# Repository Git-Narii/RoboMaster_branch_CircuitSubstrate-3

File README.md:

24Vの電源及びCAN通信の信号線を分岐させる基板

3つまでのロボマスモータに対応

裏側のみの使用

4ピンの5Vはエナメル線などで追加接続が必要

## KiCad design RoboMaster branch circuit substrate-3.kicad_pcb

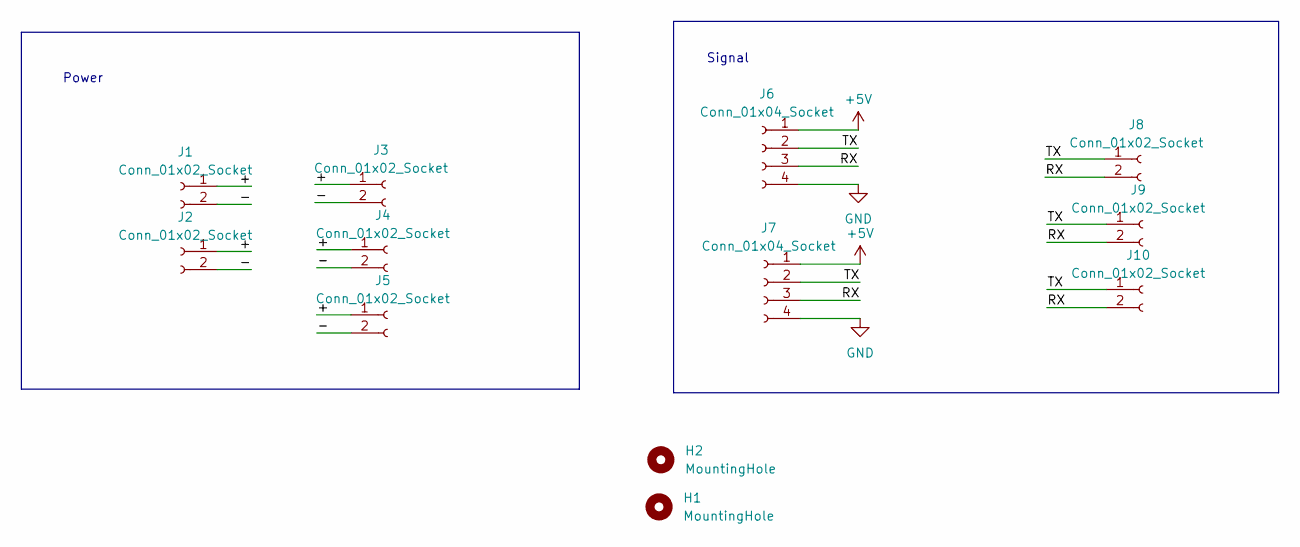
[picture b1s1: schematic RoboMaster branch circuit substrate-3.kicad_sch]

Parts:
H1, H2: MountingHole; MountingHole_3.2mm_M3
J1: Conn_01x02_Socket; AMASS_XT60PW-F_1x02_P7.20mm_Horizontal
J2: Conn_01x02_Socket; AMASS_XT60PW-M_1x02_P7.20mm_Horizontal
J3, J4, J5: Conn_01x02_Socket; AMASS_XT30U-F_1x02_P5.0mm_Vertical
J6, J7: Conn_01x04_Socket; JST_XA_S04B-XASK-1_1x04_P2.50mm_Horizontal
J8, J9, J10: Conn_01x02_Socket; JST_XA_B02B-XASK-1_1x02_P2.50mm_Vertical

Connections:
+5V: J6.1, J7.1
/+: J1.1, J2.1, J3.1, J4.1, J5.1
/-: J1.2, J2.2, J3.2, J4.2, J5.2
/RX: J6.3, J7.3, J8.2, J9.2, J10.2
/TX: J6.2, J7.2, J8.1, J9.1, J10.1
GND: J6.4, J7.4

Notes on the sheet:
Power
Signal

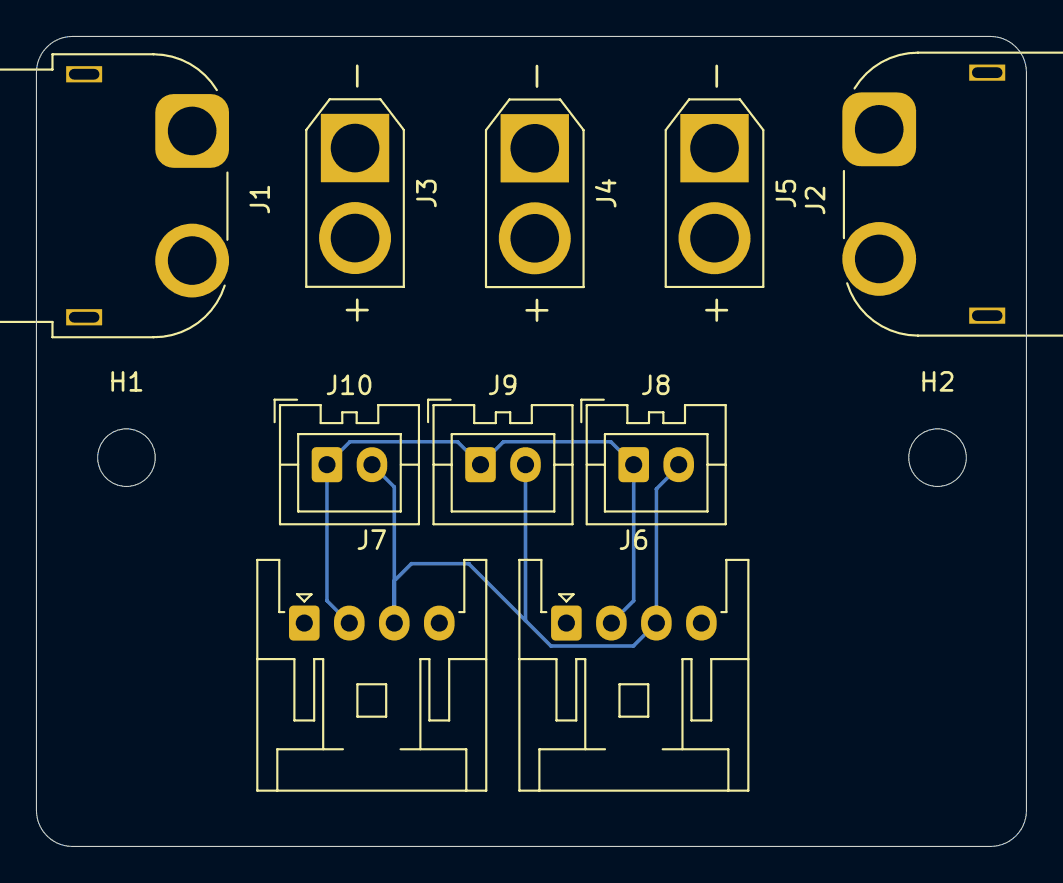
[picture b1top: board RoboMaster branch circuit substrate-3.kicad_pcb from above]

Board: 2 copper layers, 55.0 x 45.0 mm, 12 parts (0 on the bottom side), 6 nets.
